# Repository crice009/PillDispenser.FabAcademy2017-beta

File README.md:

#Pill Dispenser (working title: Novelda)
Fab Academy2017 --beta

These files build a device that will manage pills medications for someone who needs to take them on a schedule. Ideally, this machine will dispense pills and make simple efforts to through sensors and alerts (local and internet based) to avoid too much or too little medication being taken at any time. Perhaps even with medication compliance information that could be useful for better understanding the user’s behavior. My hope was to create a valuable data stream, where there was none previously. 

To give this a more personal explanation: My grandmother recently passed of Alzheimer’s disease. My family regularly worried if she was taking her medications on schedule (as it was difficult or impossible for her to remember on her own. A device like this could manage that all for her. If everything worked perfectly, a family member could place the bottle of pills in the machine and then let it run in Grandma’s home on the kitchen counter. The machine would then dispense the pills on a schedule, but actively manage so they don’t get backlogged. An alarm would help Grandma remember when it was time to take the pills. Furthermore, an internet app could track her medication compliance, and email a family member to give Grandma a call if she seems to be getting off schedule. [This is a pie-in-the-sky dream, but the project is close to having all of those features integrated as of July 2017.] The working title given above could be a simplified name for a theoretical commercial device. It is also my own beloved grandmother’s name. 

<a href='https://youtu.be/coTj5rTIzWQ'>Fab Academy 2017 Final Project Presentation (YouTube video)</a>

Hopefully, this could be useful to anyone who needs such a device. I am hoping to develop this project further when I have some time (I am a high school science teacher in the Cleveland, OH, USA area). If anyone is willing to employ me to work on this project, I would totally be happy to explore that option. I feel that this sort of a device is a public good, that should be free or cheap. The service (internet backend, data streams, user accounts, and online interfaces) are something that I would like to explore as a cheap paid service that could enhance the system’s utility and provide a revenue stream from this type of device. 

This repository will house the updated version of Corey Rice’s 2017 Fab Academy final project. Significant changes have already happened since the end of the Fab Academy class. Corey Rice maintains the copyright for this creative work, and is happy to collaborate with anyone who would like to expand on the project. Many of the pieces and parts are derived from a variety of sources, each with their own open source licenses – the majority come from Neil Gershenfeld. Names of original copyright holders in derived programs were maintained.

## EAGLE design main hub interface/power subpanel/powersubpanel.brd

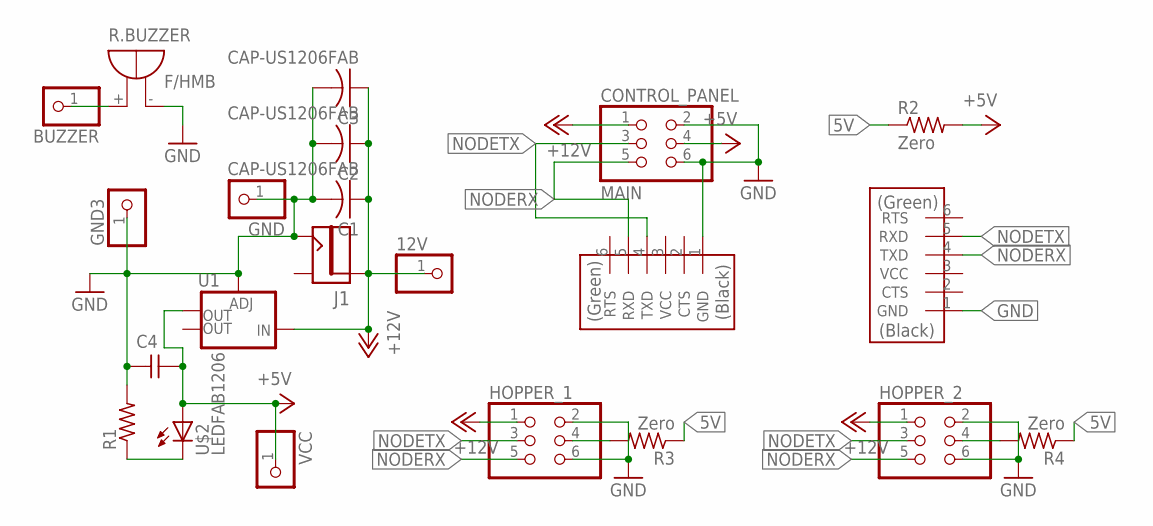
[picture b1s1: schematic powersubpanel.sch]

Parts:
12V: PINHD-1X1; 1X01
BUZZER: PINHD-1X1; 1X01
C1, C2, C3: CAP-US1206FAB; C1206FAB
C4: CAP-UNPOLARIZEDFAB; C1206FAB
CONTROL_PANEL: MAIN; 2X03SMD
FORCONTROLLER: FTDI-SMD-HEADER; 1X06SMD
FORHOPPER: FTDI-SMD-HEADER; 1X06SMD
GND, GND3: PINHD-1X1; 1X01
HOPPER_1, HOPPER_2: PINHD-2X3-SMD; 2X03SMD
J1: JACK2.1MM; JACK_2.1MM
R1: RES-US1206FAB; R1206FAB
R2, R3, R4: Zero; R1206FAB
R.BUZZER: F/HMB
U1: V_REG_LM1117SOT223; SOT223
U$2: LEDFAB1206; LED1206FAB
VCC: PINHD-1X1; 1X01

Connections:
5V: R2.1, R3.1, R4.1
5VA: HOPPER_1.4, R3.2
5VB: HOPPER_2.4, R4.2
+5V: C4.2, CONTROL_PANEL.4, R2.2, U1.4 (OUT), U$2.1 (A), VCC.1
+12V: 12V.1, C1.1, C2.1, C3.1, CONTROL_PANEL.1, HOPPER_1.1, HOPPER_2.1, J1.PIN, U1.3 (IN)
GND: C1.2, C2.2, C3.2, C4.1, CONTROL_PANEL.2, CONTROL_PANEL.6, FORCONTROLLER.1 (GND), FORHOPPER.1 (GND), GND.1, GND3.1, HOPPER_1.2, HOPPER_1.6, HOPPER_2.2, HOPPER_2.6, J1.CONTACT, R1.2, R.BUZZER.-, U1.1 (ADJ)
unnamed: BUZZER.1, R.BUZZER.+
unnamed: R1.1, U$2.2 (C)
NODERX: CONTROL_PANEL.5, FORCONTROLLER.5 (RXD), FORHOPPER.4 (TXD), HOPPER_1.5, HOPPER_2.5
NODETX: CONTROL_PANEL.3, FORCONTROLLER.4 (TXD), FORHOPPER.5 (RXD), HOPPER_1.3, HOPPER_2.3

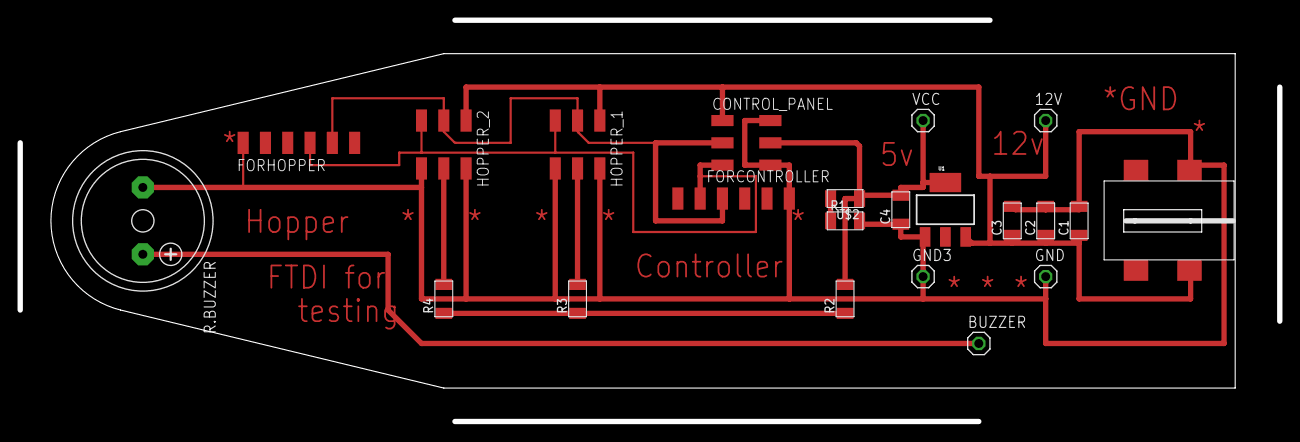
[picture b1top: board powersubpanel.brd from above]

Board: 2 copper layers, 143.5 x 45.7 mm, 22 parts (0 on the bottom side), 10 nets.

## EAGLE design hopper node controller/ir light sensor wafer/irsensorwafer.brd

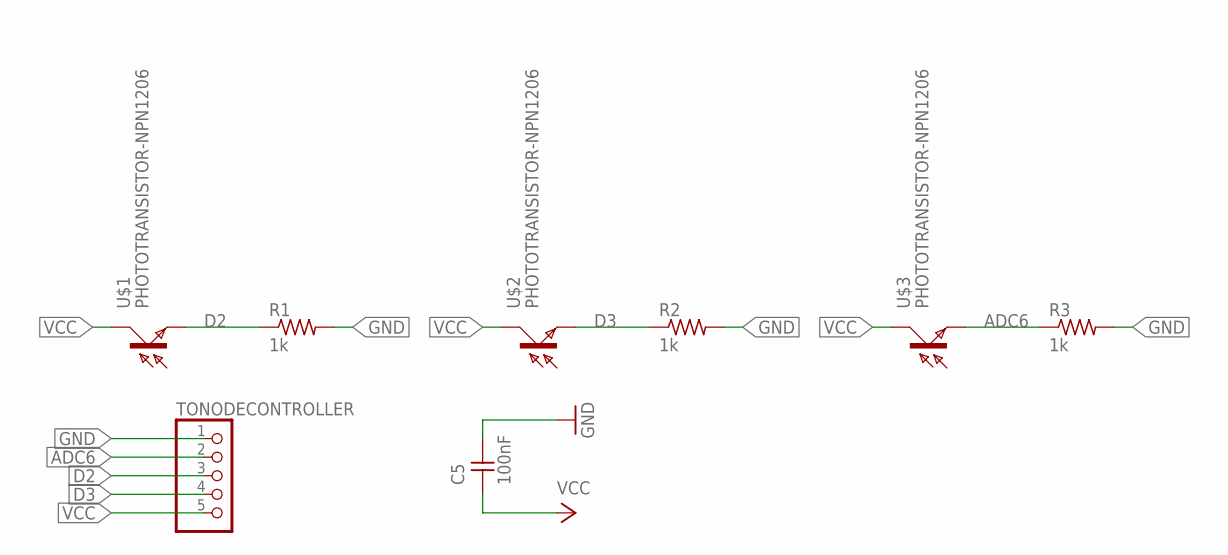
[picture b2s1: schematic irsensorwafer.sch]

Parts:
C5: 100nF; C1206FAB
R1, R2, R3: 1k; R1206FAB
TONODECONTROLLER: PINHD-1X5; 1X05
U$1, U$2, U$3: PHOTOTRANSISTOR-NPN1206; OP1206

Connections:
ADC6: R3.1, TONODECONTROLLER.2, U$3.EMITTER (E)
D2: R1.1, TONODECONTROLLER.3, U$1.EMITTER (E)
D3: R2.1, TONODECONTROLLER.4, U$2.EMITTER (E)
GND: C5.2, R1.2, R2.2, R3.2, TONODECONTROLLER.1
VCC: C5.1, TONODECONTROLLER.5, U$1.COLLECTOR (C), U$2.COLLECTOR (C), U$3.COLLECTOR (C)

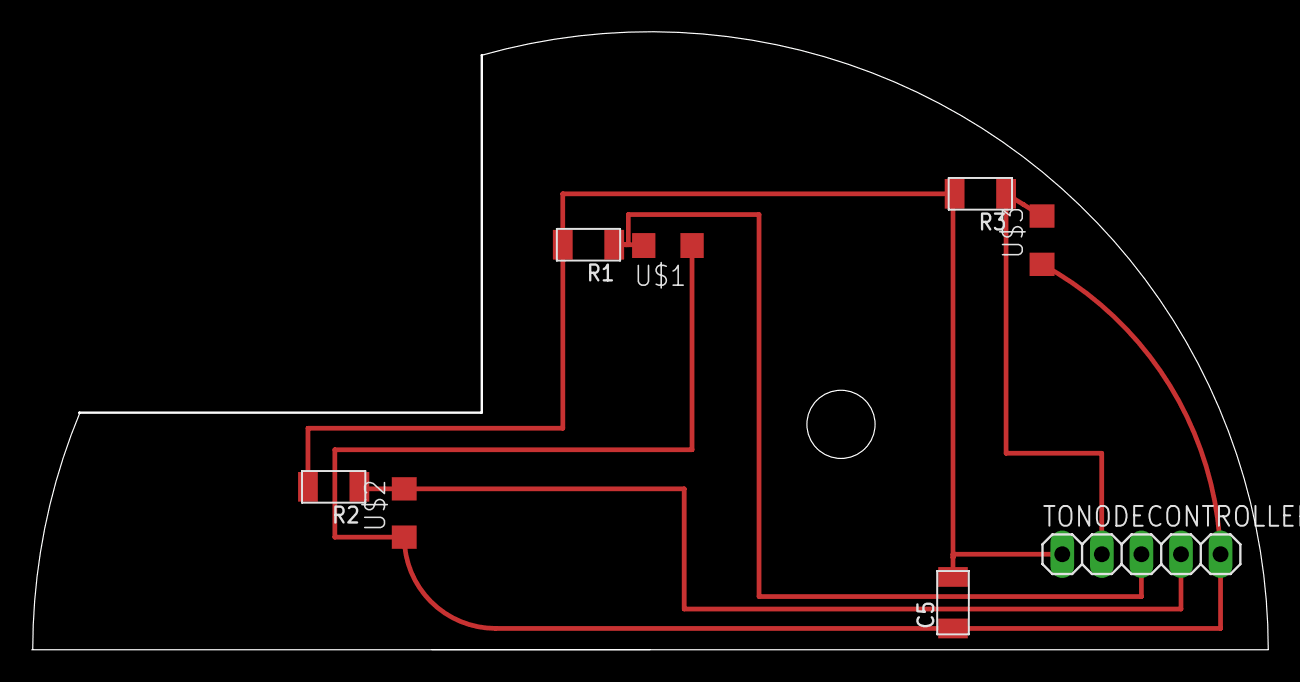
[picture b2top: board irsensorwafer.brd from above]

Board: 2 copper layers, 79.3 x 39.6 mm, 8 parts (0 on the bottom side), 5 nets.

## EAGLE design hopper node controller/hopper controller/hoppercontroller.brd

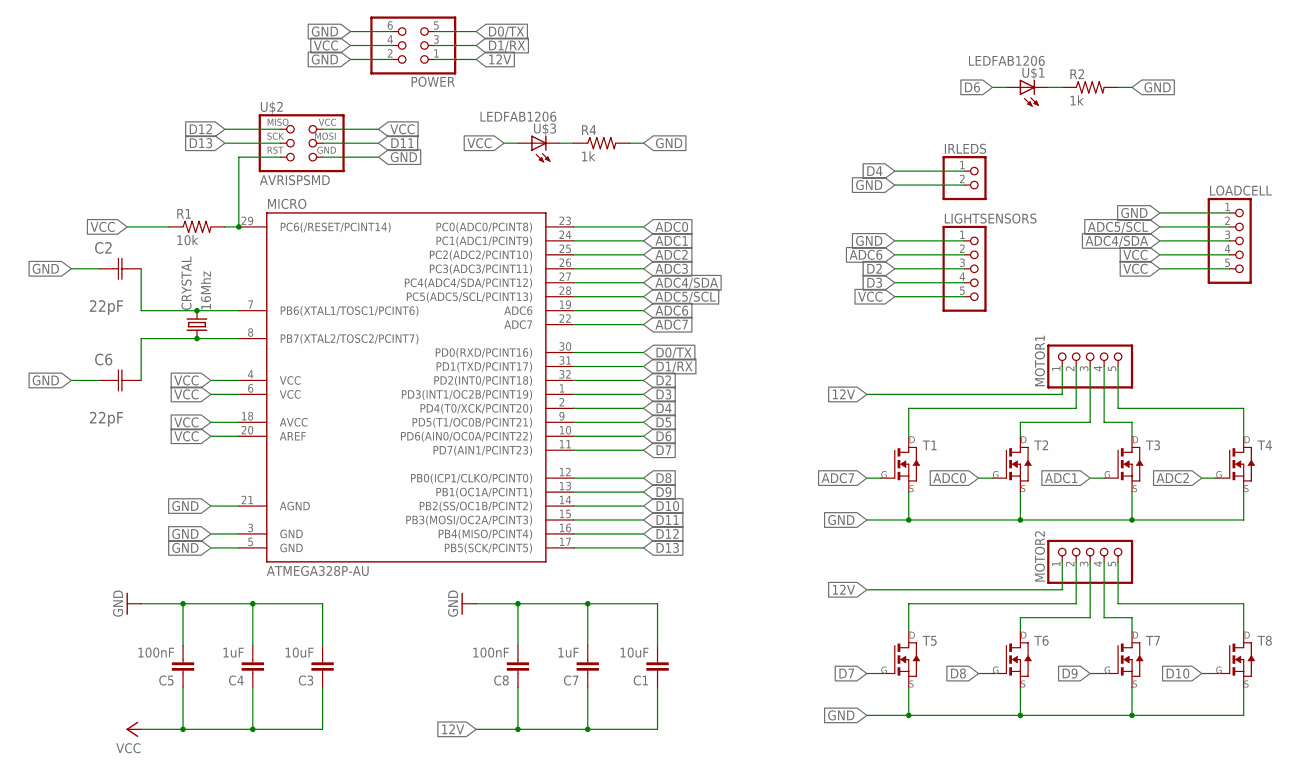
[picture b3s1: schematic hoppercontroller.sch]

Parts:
C1, C3: 10uF; 1206
C2, C6: 22pF; CAPC3216X178N
C4, C7: 1uF; 1206
C5, C8: 100nF; 1206
CRYSTAL: 16Mhz; CSM-7X-DU
IRLEDS: PINHD-1X2; 1X02
LIGHTSENSORS: PINHD-1X5; 1X05
LOADCELL: PINHD-1X5; 1X05
MICRO: ATMEGA328P-AU; TQFP32-08
MOTOR1, MOTOR2: PINHD-1X5; 1X05
POWER: PINHD-2X3-SMD; 2X03SMD
R1: 10k; 1206
R2, R4: 1k; R1206FAB
T1, T2, T3, T4, T5, T6, T7, T8: NMOSFETTO252; TO252
U$1, U$3: LEDFAB1206; LED1206FAB
U$2: AVRISPSMD; 2X03SMD

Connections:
12V: C1.1, C7.1, C8.1, MOTOR1.1, MOTOR2.1, POWER.1
ADC0: MICRO.23 (PC0(ADC0/PCINT8)), T2.1 (G)
ADC1: MICRO.24 (PC1(ADC1/PCINT9)), T3.1 (G)
ADC2: MICRO.25 (PC2(ADC2/PCINT10)), T4.1 (G)
ADC3: MICRO.26 (PC3(ADC3/PCINT11))
ADC4/SDA: LOADCELL.3, MICRO.27 (PC4(ADC4/SDA/PCINT12))
ADC5/SCL: LOADCELL.2, MICRO.28 (PC5(ADC5/SCL/PCINT13))
ADC6: LIGHTSENSORS.2, MICRO.19 (ADC6)
ADC7: MICRO.22 (ADC7), T1.1 (G)
D0/TX: MICRO.30 (PD0(RXD/PCINT16)), POWER.5
D1/RX: MICRO.31 (PD1(TXD/PCINT17)), POWER.3
D2: LIGHTSENSORS.3, MICRO.32 (PD2(INT0/PCINT18))
D3: LIGHTSENSORS.4, MICRO.1 (PD3(INT1/OC2B/PCINT19))
D4: IRLEDS.1, MICRO.2 (PD4(T0/XCK/PCINT20))
D5: MICRO.9 (PD5(T1/OC0B/PCINT21))
D6: MICRO.10 (PD6(AIN0/OC0A/PCINT22)), U$1.1 (A)
D7: MICRO.11 (PD7(AIN1/PCINT23)), T5.1 (G)
D8: MICRO.12 (PB0(ICP1/CLKO/PCINT0)), T6.1 (G)
D9: MICRO.13 (PB1(OC1A/PCINT1)), T7.1 (G)
D10: MICRO.14 (PB2(SS/OC1B/PCINT2)), T8.1 (G)
D11: MICRO.15 (PB3(MOSI/OC2A/PCINT3)), U$2.4 (MOSI)
D12: MICRO.16 (PB4(MISO/PCINT4)), U$2.1 (MISO)
D13: MICRO.17 (PB5(SCK/PCINT5)), U$2.3 (SCK)
GND: C1.2, C2.1 (C1), C3.2, C4.2, C5.2, C6.1 (C1), C7.2, C8.2, IRLEDS.2, LIGHTSENSORS.1, LOADCELL.1, MICRO.3 (GND), MICRO.5 (GND), MICRO.21 (AGND), POWER.2, POWER.6, R2.2, R4.2, T1.2 (S), T2.2 (S), T3.2 (S), T4.2 (S), T5.2 (S), T6.2 (S), T7.2 (S), T8.2 (S), U$2.6 (GND)
unnamed: MOTOR2.3, T6.3 (D)
unnamed: MOTOR1.3, T2.3 (D)
unnamed: MICRO.29 (PC6(/RESET/PCINT14)), R1.2, U$2.5 (RST)
unnamed: C2.2 (C2), CRYSTAL.2, MICRO.7 (PB6(XTAL1/TOSC1/PCINT6))
unnamed: MOTOR1.2, T1.3 (D)
unnamed: MOTOR1.4, T3.3 (D)
unnamed: R4.1, U$3.2 (C)
unnamed: MOTOR1.5, T4.3 (D)
unnamed: MOTOR2.2, T5.3 (D)
unnamed: MOTOR2.4, T7.3 (D)
unnamed: MOTOR2.5, T8.3 (D)
unnamed: C6.2 (C2), CRYSTAL.1, MICRO.8 (PB7(XTAL2/TOSC2/PCINT7))
unnamed: R2.1, U$1.2 (C)
VCC: C3.1, C4.1, C5.1, LIGHTSENSORS.5, LOADCELL.4, LOADCELL.5, MICRO.4 (VCC), MICRO.6 (VCC), MICRO.18 (AVCC), MICRO.20 (AREF), POWER.4, R1.1, U$2.2 (VCC), U$3.1 (A)

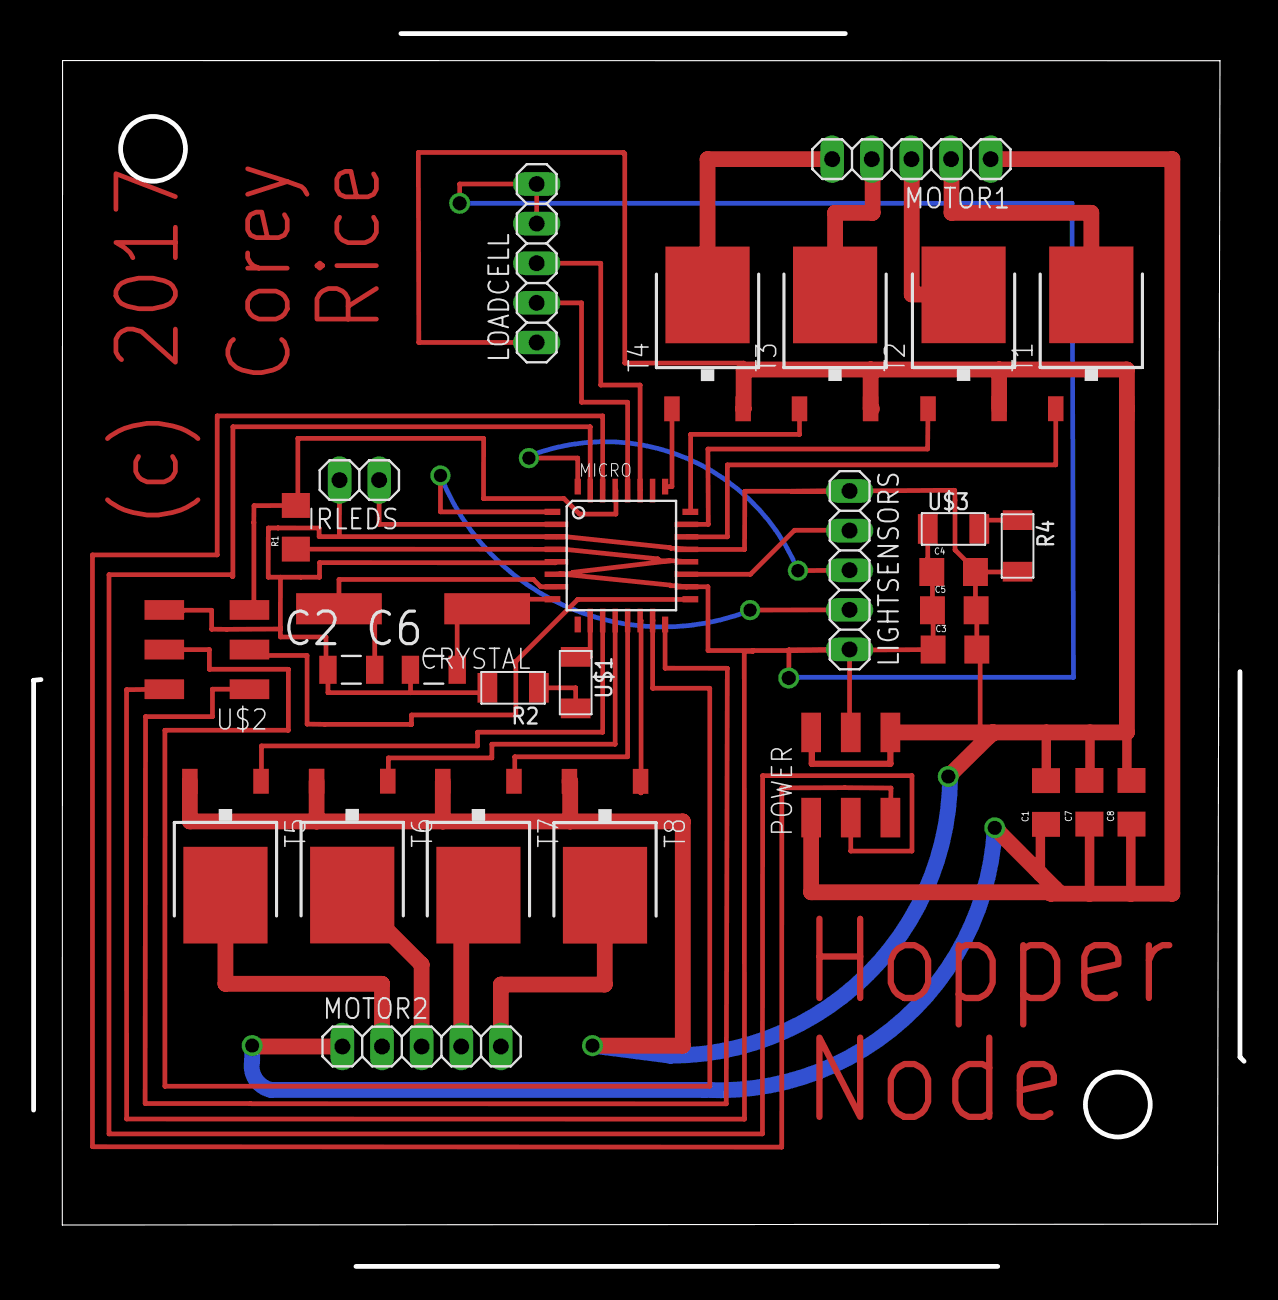
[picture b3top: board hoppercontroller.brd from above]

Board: 2 copper layers, 77.6 x 79.0 mm, 30 parts (0 on the bottom side), 36 nets.

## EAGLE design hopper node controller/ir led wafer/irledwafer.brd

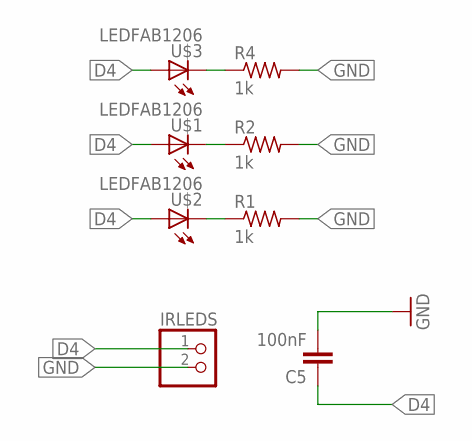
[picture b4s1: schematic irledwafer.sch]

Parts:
C5: 100nF; 1206
IRLEDS: PINHD-1X2; 1X02
R1, R2, R4: 1k; R1206FAB
U$1, U$2, U$3: LEDFAB1206; LED1206FAB

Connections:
D4: C5.1, IRLEDS.1, U$1.1 (A), U$2.1 (A), U$3.1 (A)
GND: C5.2, IRLEDS.2, R1.2, R2.2, R4.2
unnamed: R1.1, U$2.2 (C)
unnamed: R4.1, U$3.2 (C)
unnamed: R2.1, U$1.2 (C)

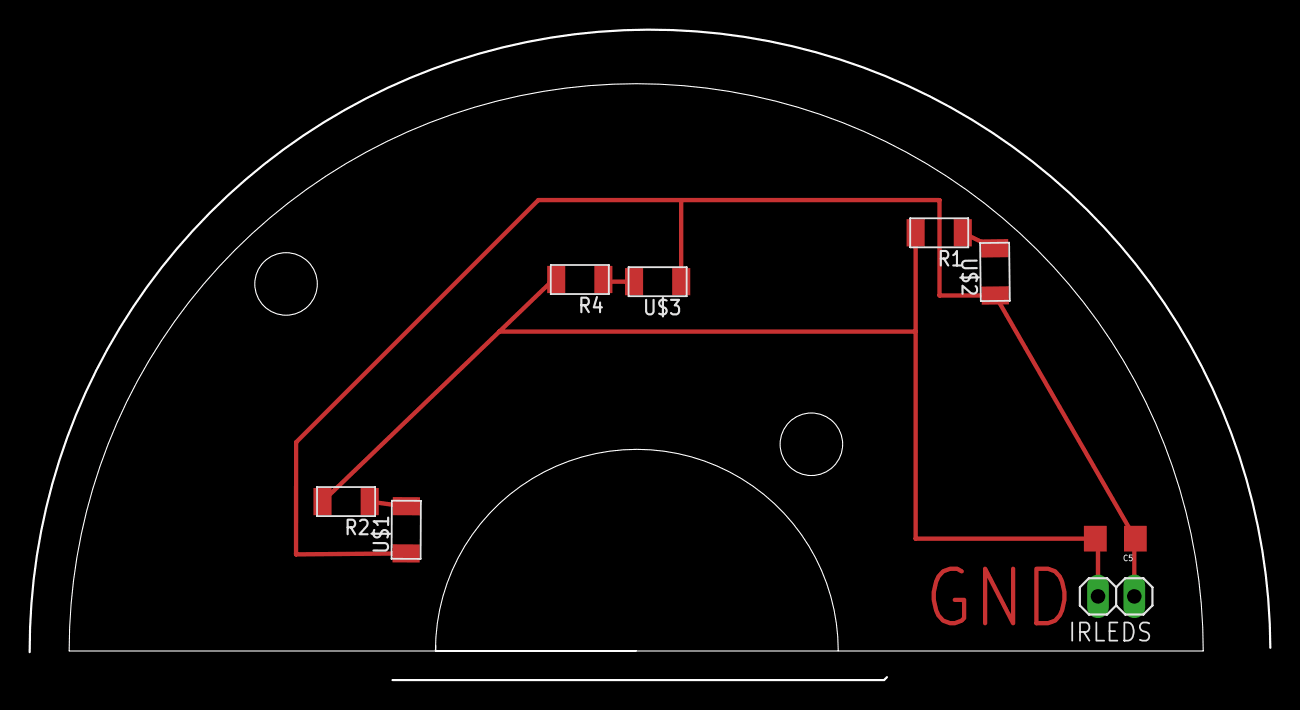
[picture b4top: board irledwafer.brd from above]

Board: 2 copper layers, 86.8 x 45.5 mm, 8 parts (0 on the bottom side), 5 nets.

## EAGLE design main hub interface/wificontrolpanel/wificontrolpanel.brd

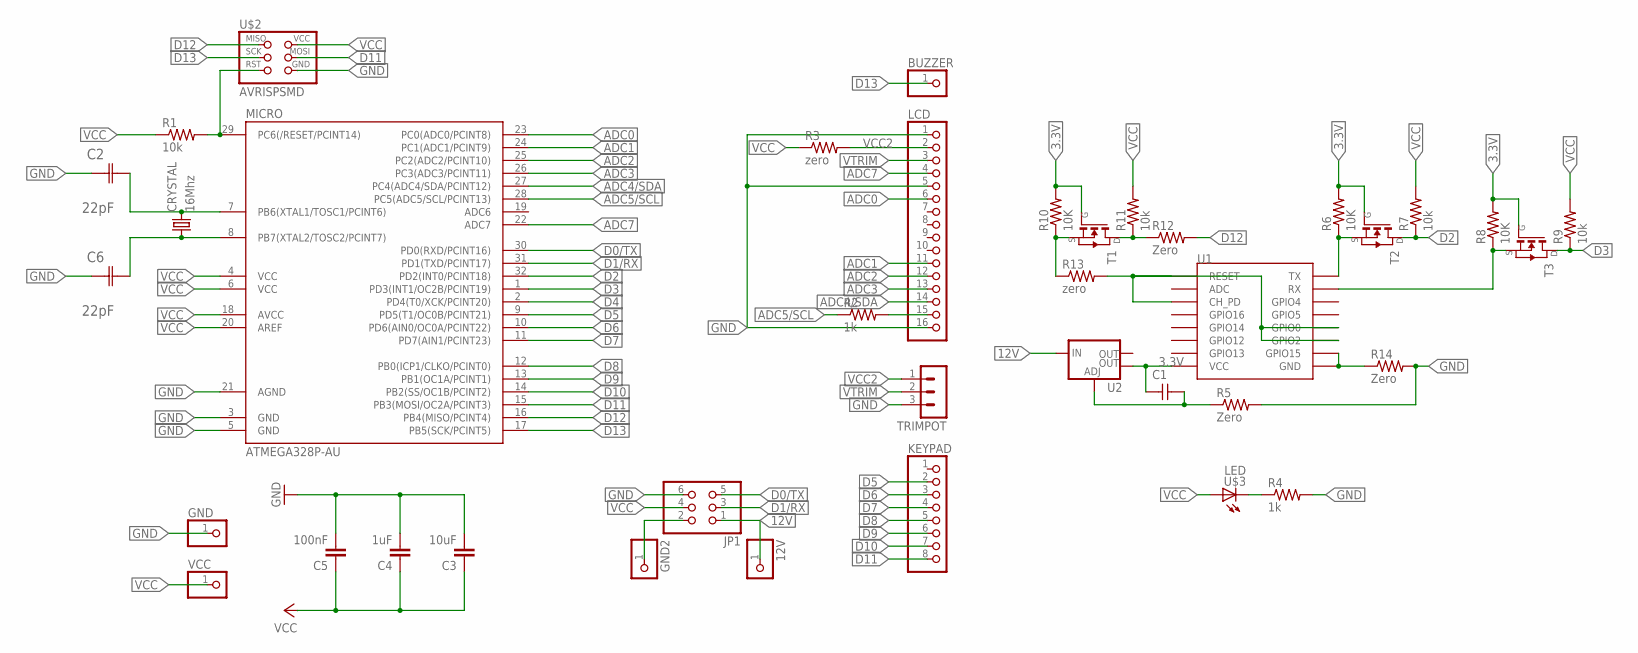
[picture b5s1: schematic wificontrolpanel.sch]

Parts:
12V: PINHD-1X1; 1X01
BUZZER: PINHD-1X1; 1X01
C1: CAP-UNPOLARIZEDFAB; C1206FAB
C2, C6: 22pF; CAPC3216X178N
C3: 10uF; 1206
C4: 1uF; 1206
C5: 100nF; 1206
CRYSTAL: 16Mhz; CSM-7X-DU
GND, GND2: PINHD-1X1; 1X01
JP1: PINHD-2X3-SMD; 2X03SMD
KEYPAD: PINHD-1X8; 1X08
LCD: PINHD-1X16; 1X16
MICRO: ATMEGA328P-AU; TQFP32-08
R1: 10k; 1206
R2: 1k; R1206FAB
R3, R13: zero; R1206FAB
R4: 1k; R1206
R5, R12, R14: Zero; R1206FAB
R6, R8, R10: 10K; R1206FAB
R7, R9, R11: 10k; R1206FAB
T1, T2, T3: NMOSFETSOT23; SOT-23
TRIMPOT: MA03-1
U1: ESP12SMD; ESP12-SMD
U2: V_REG_LM1117SOT223; SOT223
U$2: AVRISPSMD; 2X03SMD
U$3: LED; LED1206
VCC: PINHD-1X1; 1X01

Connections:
3.3V: C1.1, R6.2, R8.2, R10.2, T1.3 (G), T2.3 (G), T3.3 (G), U1.VCC, U2.4 (OUT)
12V: 12V.1, JP1.1, U2.3 (IN)
ADC0: LCD.6, MICRO.23 (PC0(ADC0/PCINT8))
ADC1: LCD.11, MICRO.24 (PC1(ADC1/PCINT9))
ADC2: LCD.12, MICRO.25 (PC2(ADC2/PCINT10))
ADC3: LCD.13, MICRO.26 (PC3(ADC3/PCINT11))
ADC4/SDA: LCD.14, MICRO.27 (PC4(ADC4/SDA/PCINT12))
ADC5/SCL: MICRO.28 (PC5(ADC5/SCL/PCINT13)), R2.1
ADC7: LCD.4, MICRO.22 (ADC7)
D0/TX: JP1.5, MICRO.30 (PD0(RXD/PCINT16))
D1/RX: JP1.3, MICRO.31 (PD1(TXD/PCINT17))
D2: MICRO.32 (PD2(INT0/PCINT18)), R7.1, T2.1 (D)
D3: MICRO.1 (PD3(INT1/OC2B/PCINT19)), R9.1, T3.1 (D)
D4: MICRO.2 (PD4(T0/XCK/PCINT20))
D5: KEYPAD.2, MICRO.9 (PD5(T1/OC0B/PCINT21))
D6: KEYPAD.3, MICRO.10 (PD6(AIN0/OC0A/PCINT22))
D7: KEYPAD.4, MICRO.11 (PD7(AIN1/PCINT23))
D8: KEYPAD.5, MICRO.12 (PB0(ICP1/CLKO/PCINT0))
D9: KEYPAD.6, MICRO.13 (PB1(OC1A/PCINT1))
D10: KEYPAD.7, MICRO.14 (PB2(SS/OC1B/PCINT2))
D11: KEYPAD.8, MICRO.15 (PB3(MOSI/OC2A/PCINT3)), U$2.4 (MOSI)
D12: MICRO.16 (PB4(MISO/PCINT4)), R12.2, U$2.1 (MISO)
D13: BUZZER.1, MICRO.17 (PB5(SCK/PCINT5)), U$2.3 (SCK)
GND: C2.1 (C1), C3.2, C4.2, C5.2, C6.1 (C1), GND.1, JP1.6, LCD.1, LCD.5, LCD.16, MICRO.3 (GND), MICRO.5 (GND), MICRO.21 (AGND), R4.2, R5.2, R14.2, TRIMPOT.3, U$2.6 (GND)
GND2: GND2.1, JP1.2
GND3: C1.2, R5.1, U2.1 (ADJ)
GND4: R14.1, U1.GND, U1.GPIO15
unnamed: MICRO.29 (PC6(/RESET/PCINT14)), R1.2, U$2.5 (RST)
unnamed: C2.2 (C2), CRYSTAL.2, MICRO.7 (PB6(XTAL1/TOSC1/PCINT6))
unnamed: R6.1, T2.2 (S), U1.TXD0 (TX)
unnamed: LCD.15, R2.2
unnamed: R4.1, U$3.2 (C)
unnamed: R8.1, T3.2 (S), U1.RXD0 (RX)
unnamed: R10.1, R13.1, T1.2 (S)
unnamed: R13.2, U1.CH_PD, U1.GPIO0, U1.GPIO2, U1.RESET
unnamed: R11.1, R12.1, T1.1 (D)
unnamed: C6.2 (C2), CRYSTAL.1, MICRO.8 (PB7(XTAL2/TOSC2/PCINT7))
VCC: C3.1, C4.1, C5.1, JP1.4, MICRO.4 (VCC), MICRO.6 (VCC), MICRO.18 (AVCC), MICRO.20 (AREF), R1.1, R3.1, R7.2, R9.2, R11.2, U$2.2 (VCC), U$3.1 (A), VCC.1
VCC2: LCD.2, R3.2, TRIMPOT.1
VTRIM: LCD.3, TRIMPOT.2

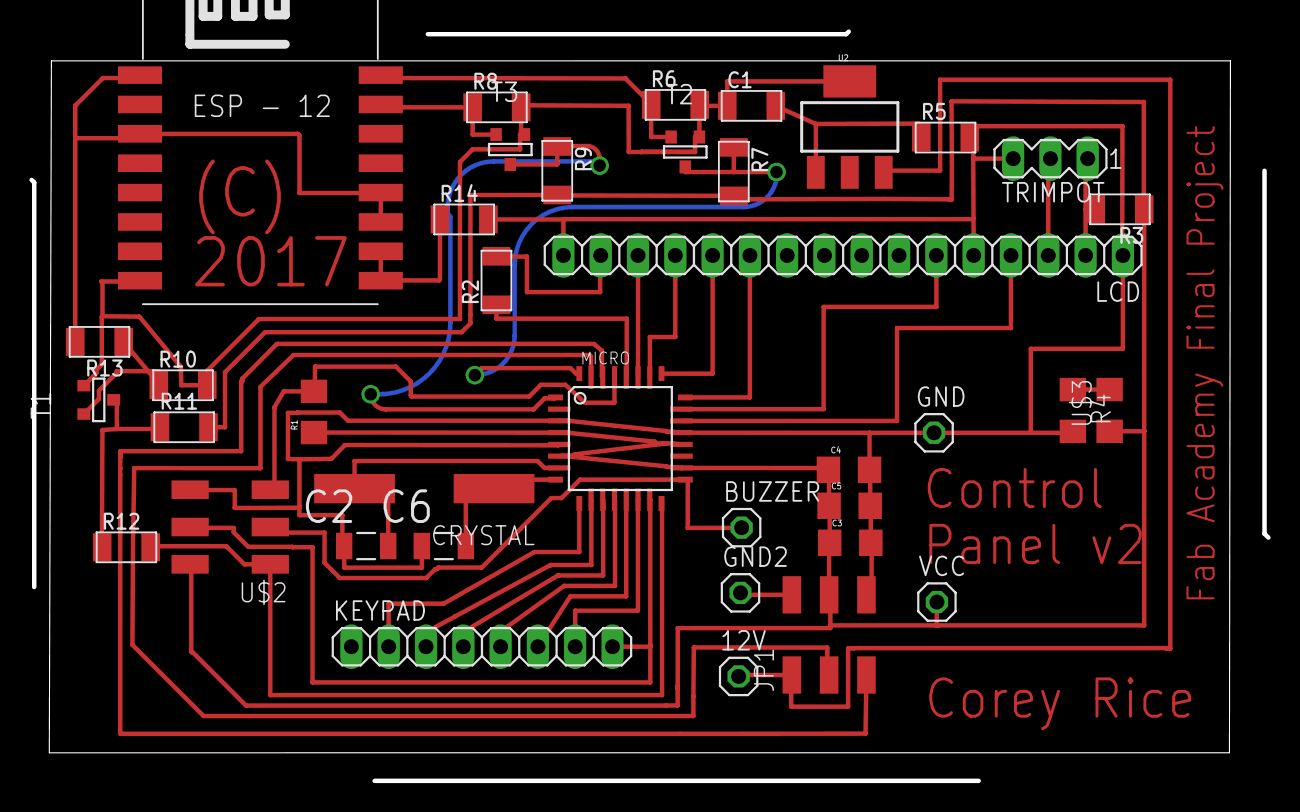
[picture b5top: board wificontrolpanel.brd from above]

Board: 2 copper layers, 84.2 x 51.0 mm, 38 parts (0 on the bottom side), 39 nets.

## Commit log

2017-07-22 Create LICENSE.md
    license change
2017-07-24 inital upload and description

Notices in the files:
hopper node controller/hopper controller/hoppercontroller.brd:
(c) 2017
parts and their libraries:
01_SparkFun: Licensing: CC v3.0 Share-Alike You are welcome to use this library for commercial purposes.
